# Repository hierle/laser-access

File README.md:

# laser-access

An access system for a laser cutter (or any other electric system), based on Arduino, ESP8266 Wifi and NFC reader and member cards.
Easy update of tag database via Wifi link to a central user db. This is running just fine for a while here at Fablab Munich :)

* [./eagle](https://github.com/hierle/laser-access/eagle/) &nbsp;&nbsp;&nbsp;&nbsp;&nbsp; PCB (eagle) files for custom shield
* [./housing](https://github.com/hierle/laser-access/housing/) &nbsp;&nbsp;&nbsp; DXF drawing for laser cut housing
* [./laser_access](https://github.com/hierle/laser-access/laser_access/) &nbsp; Arduino software

The software is running on an Arduino Mega 2560, packed with a "shield" (eagle files included),
holding breakout modules for RTC, NFC, Wifi (ESP8862-1), I2C-EEPROM and TFT touch display.

It's reading NFC (Mifare) cards dropped in, comparing the serial to a database in internal eeprom,
granting access to known serials only. If the tag serial number is found in eeprom database, then
- the 230V main relais of the laser cutter is turned on
- user name and phone number (both stored on the card) are displayed

If the dedicated "update card" is seen, the database (of allowed card serial numbers) is downloaded from a (Raspberry Pi) Wifi access point.

Internal 4k eeprom of the Mega board allows for up to 1000 users, external EEPROM holds up to 64kBytes log events.

Libraries used:

- https://github.com/adafruit/Adafruit_NFCShield_I2C
- https://github.com/adafruit/Adafruit-GFX-Library
- https://github.com/adafruit/Adafruit_ILI9341
- https://github.com/adafruit/Adafruit_STMPE610

Have fun :)

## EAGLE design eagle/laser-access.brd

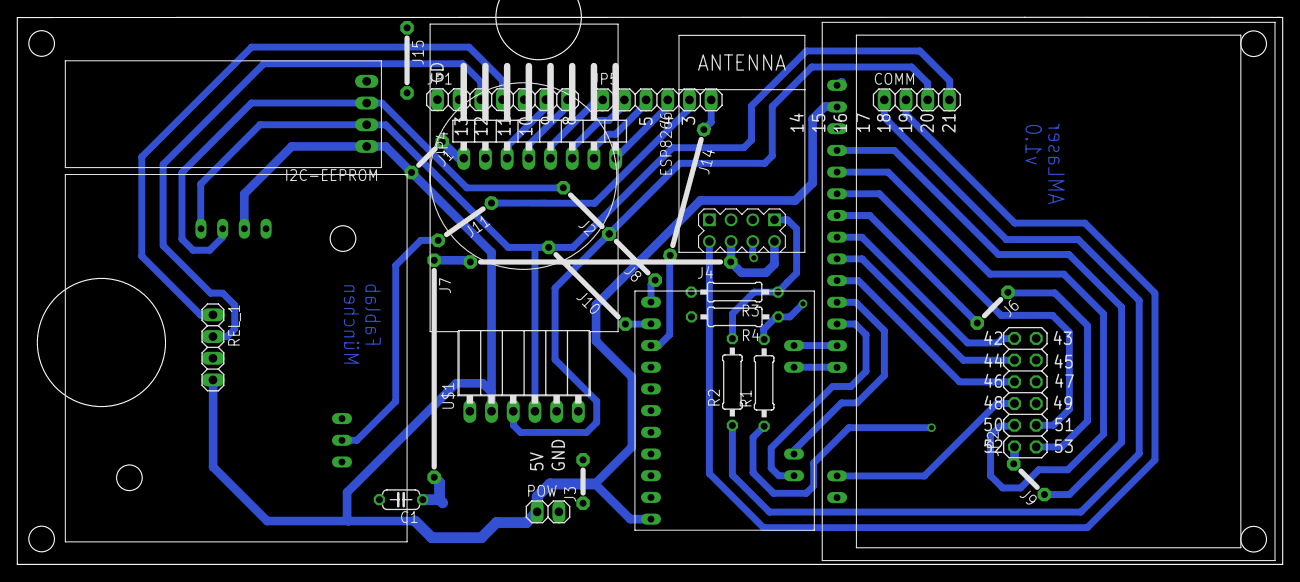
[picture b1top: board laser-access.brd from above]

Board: 2 copper layers, 148.1 x 64.0 mm, 31 parts (1 on the bottom side), 32 nets.

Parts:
C1: C050-024X044
COMM: 1X04
ESP8266: WIRELESS-WIFI-ESP-01
I2C-EEPROM: I2C-EEPROM
IC2: LD117AS33TR; SOT223
J1, J3, J6, J9: J5MM; 05
J2, J8, J11, J15: J7MM; 07
J4: J30MM; 30
J7: J25MM; 25
J10: J12MM; 12
J14: J15MM; 15
JP1: 1X07
JP2: 2X06
JP4: 1X08/90
JP5: 1X06
POW: 1X02
R1, R2: 10k; 0207/10
R3, R4: 20k; 0207/10
REL_1: 1X04
U$1: I2C-RTC
U$3: TFT-2.4-SPI; TFT-SPI-2.4
U$4: I2C-NFC-V3
U$6: R-TOUCH

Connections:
42: JP2.12, U$3.DC
43: JP2.11, R1.1
44: JP2.10, U$3.RST
46: JP2.8, U$3.LITE
48: JP2.6, U$3.CCS
50: JP2.4, U$3.MISO
51: JP2.3, U$3.MOSI
52: J9.1, J9.2, JP2.2, U$3.CLK
53: J6.1, J6.2, JP2.1, U$3.CS
+3V3: C1.1, ESP8266.B2, ESP8266.D2, IC2.4, J4.1, J4.2, J7.1, J7.2
+5V: I2C-EEPROM.+5V, IC2.3, J1.1, J1.2, JP4.1, POW.1, REL_1.4, U$1.+5V, U$3.+5V, U$4.+5V, U$6.+5V
D2: J14.1, J14.2, JP5.6, U$6.IRQ
D3: J11.1, J11.2, JP5.5, U$4.IRQ
D4: JP4.8, JP5.4
D5: JP4.7, JP5.3
D6: JP4.6, JP5.2
D7: JP4.5, JP5.1
D8: JP1.7, JP4.4
D9: JP1.6, JP4.3
D11: JP1.4, REL_1.1
D12: JP1.3, REL_1.2
ESPRST: ESP8266.C2, R1.2, R4.1
ESP_RX: ESP8266.D1, R2.2, R3.1
GND: C1.2, ESP8266.A1, I2C-EEPROM.GND, IC2.1, J3.1, J3.2, J15.1, J15.2, JP1.1, JP4.2, POW.2, R3.2, R4.2, REL_1.3, U$1.GND, U$3.GND, U$4.GND, U$4.GND2, U$6.GND, U$6.MODE
RXD1: COMM.2, ESP8266.A2
SCL: COMM.4, I2C-EEPROM.SCL, J10.1, J10.2, U$1.SCL, U$4.SCL, U$6.SCL
SDA: COMM.3, I2C-EEPROM.SDA, J2.1, J2.2, J8.1, J8.2, U$1.SDA, U$4.SDA, U$6.SDA
TXD1: COMM.1, R2.1
X+: U$3.X+, U$6.X+
X-: U$3.X-, U$6.X-
Y+: U$3.Y+, U$6.Y+
Y-: U$3.Y-, U$6.Y-

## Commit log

2016-01-19 updated repo description
2016-01-19 inital commit
2016-01-19 added eagle schematic and board files
2016-01-19 added housing dxf

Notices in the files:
parts and their libraries:
diy-modules: Released under the Creative Commons Attribution 4.0 International License: http://creativecommons.org/licenses/by/4.0
